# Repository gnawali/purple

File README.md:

# What is this repository for #

This repository contains hardware and software for building practical Visible Light Communication system. The PURPLE board is a cape that works with BeagleBone Black embedded computer. With PURPLE, one can send and receive information using visible light.

The hardware design is available in the eagle folder.

### What's included ###
* Firmware running on PRU including both transmitter and receiver
* User-space program to run on embedded Linux environment 
* Hardware schematic
* Partlist to assemble your own cape [Digi-Key](http://www.digikey.com/short/qq17qj)
* PCB ordering [OSH Park](https://oshpark.com/shared_projects/B5KA0qL4)

### Contents ###

* config/

 This directory contains all configuration files used before make.

* docs/

 This directory contains all documents and notes used as instructions and tutorials deployed in class.

* example/

 This directory contains the userspace program to send and receive msgs through light.

* firmware/

 This directory contains the binary files that's going to run on PRU

* pcb/

 This directory contains the hardware schematic and the PCB layout as well as the partlists.

* src/

 This directory contains the source file that needs to be compiled into the binary file under firmware folder.

* test/

 This directory contains the test and debugging file in user space for the PRU source code.

### How do I get set up? ###

- Summary of set up
    1. Hardware
    	- Beaglebone Black
    	- Purple Cape
    	- SD card
    	- Micro USB cable
    2. Software
	    - BBB Driver[[Windows]](https://learn.adafruit.com/ssh-to-beaglebone-black-over-usb/installing-drivers-windows)[[Mac]](https://learn.adafruit.com/ssh-to-beaglebone-black-over-usb/installing-drivers-mac)[[Linux]](https://learn.adafruit.com/ssh-to-beaglebone-black-over-usb/installing-drivers-linux)
	    - SSH[[Windows]](https://learn.adafruit.com/ssh-to-beaglebone-black-over-usb/ssh-with-windows-and-putty)[[Mac/Linux]](https://learn.adafruit.com/ssh-to-beaglebone-black-over-usb/ssh-on-mac-and-linux) 
    3. Internet Connection (optional)
	    - Ethernet Cable (Required physical access to the LAN port of your router/access point)
	    - [Wireless Dongle](https://learn.adafruit.com/setting-up-wifi-with-beaglebone-black/overview)
    
* Configuration
* Dependencies
* Deployment instructions
  1. LED installation.
  2. Photodiode installation.

### How to get started ###

Step 1: Insert SD card to BBB board. Make sure SD card has been flashed with the purple image.

Step 2: Boot Up the BBB board and connect the board to your PC/Laptop. Make sure you have successfully installed the drivers for BBB.

Step 3: SSH to the board. ssh debian@192.168.7.2

```
ssh debian@192.168.7.2
```
Step 4: When you login, Change to root.

```
sudo -s
```

Step 5: Go to purple repository.

```
cd purple
```

Step 6: Reload the pru remoteproc kernel module.

```
rmmod pru_rproc

modprobe pru_rproc

```

Step 7: Compile the code.
```
make clean
make
```
Step 8: Make sure the code got compiled succesfully.

Step 9: Start listening on incoming messages on one purple board.
```
cd example
./receive
```

Step 10: Start sending the messages on other purple board.
```
cd example
./send "hello world"
```

Step 11: Make sure the message got received correctly.

Step 12: Congratulations. You've completed this short tutorial.

### Who do I talk to? ###

* Shengrong Yin (syin@uh.edu) 
* Omprakash Gnawali (gnawali@cs.uh.edu) 

### References ###

[Exploring Beaglebone](http://exploringbeaglebone.com/chapter13/)

[PRU-ICSS](http://processors.wiki.ti.com/index.php/PRU-ICSS)

[PRU-software-support-package](https://git.ti.com/pru-software-support-package)

[spruhv7a](http://www.ti.com/lit/ug/spruhv7a/spruhv7a.pdf)

[arduino VLC](https://github.com/jpiat/arduino)

[PRU mailing list](https://groups.google.com/forum/#!forum/beagleboard)

[BeagleScope](https://github.com/ZeekHuge/BeagleScope)

[PRUDAQ](https://github.com/google/prudaq/wiki)

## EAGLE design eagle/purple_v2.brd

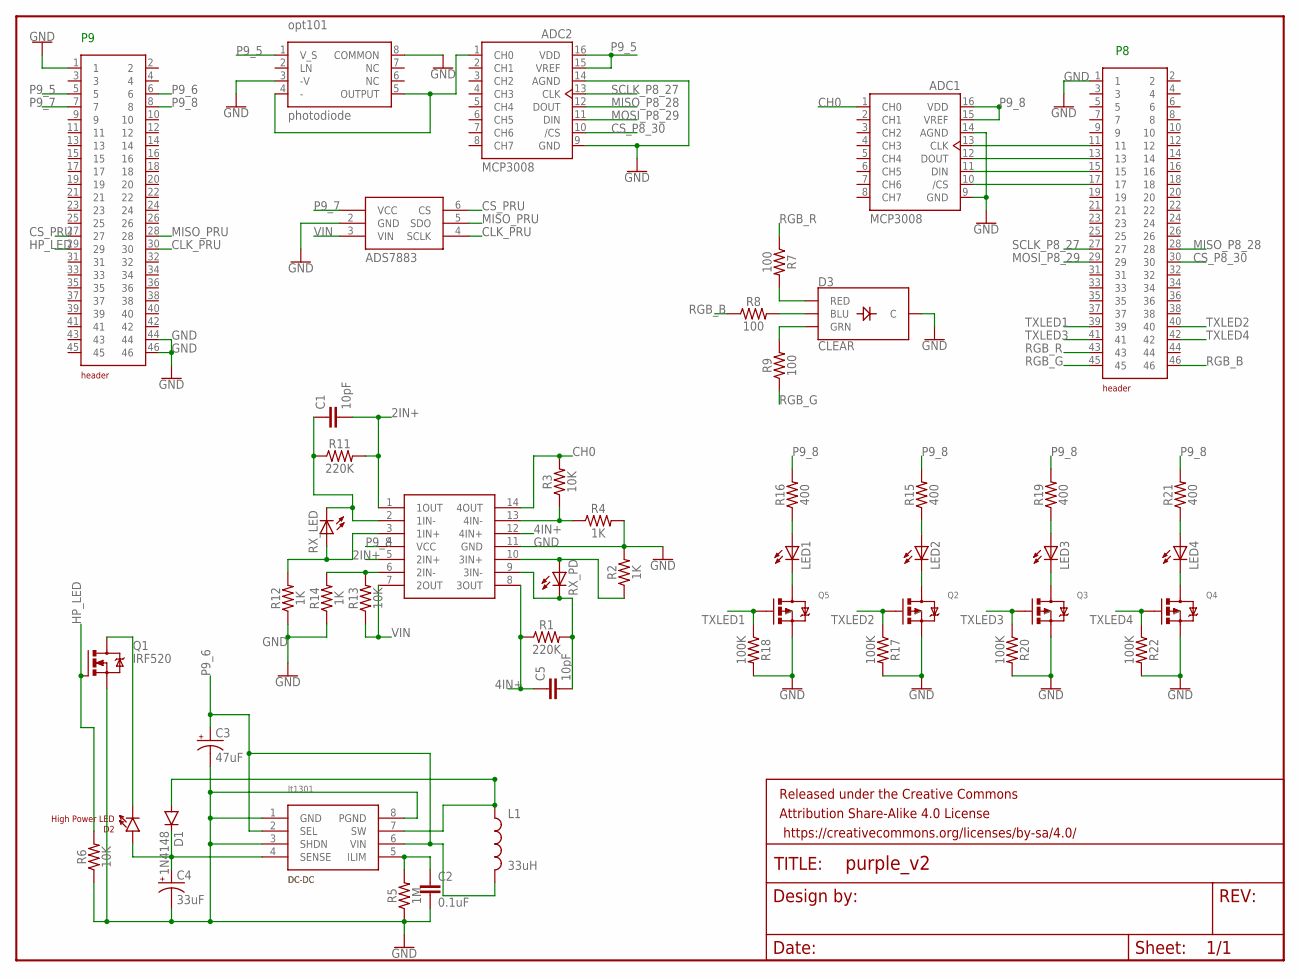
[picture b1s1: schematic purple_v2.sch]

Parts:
ADC1, ADC2: MCP3008-SO16; SO16
C1, C5: 10pF; 0603
C2: 0.1uF; CAP-PTH-SMALL
C3: 47uF; CPOL-RADIAL-10UF-25V
C4: 33uF; CPOL-RADIAL-10UF-25V
D1: 1N4148; DIODE-1N4148
D2: High Power LED; LTE-302
D3: CLEAR; LED-RGB-THRU
FRAME1: FRAME-LETTERNO_PACKAGE; DUMMY
J1, J2: 223; 2*23
L1: 33uH; RLB0912
LED1, LED2, LED3, LED4: LED5MM
OP-AMP: TLC2274-SO14; SO14
Q1: IRF520; TO220BV
Q2, Q3, Q4, Q5: MOSFET-PCHANNEL; SOT23-3
R1, R11: 220K; 0805
R2, R4, R12, R14: 1K; 0805
R3, R6, R13: 10K; 0805
R5: 1M; 0805
R7, R8, R9: 100; 0805
R15, R16, R19, R21: 400; 0805
R17, R18, R20, R22: 100K; 0805
RX_LED: LED5MM
RX_PD: LED5MM
U5: LT1301; DIL08
U9: OPT101
U$1: ADS7883; SOT23-6

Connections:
2IN+: C1.2, OP-AMP.1 (1OUT), OP-AMP.5 (2IN+), R11.2
4IN+: C5.1, OP-AMP.8 (3OUT), OP-AMP.12 (4IN+), R1.1
CH0: ADC1.1 (CH0), OP-AMP.14 (4OUT), R3.2
CLK_1: ADC1.13 (CLK), J2.11
CLK_PRU: J1.30, U$1.4 (SCLK)
CS_1: ADC1.10 (/CS), J2.17
CS_P8_30: ADC2.10 (/CS), J2.30
CS_PRU: J1.27, U$1.6 (CS)
DIN_1: ADC1.11 (DIN), J2.15
DOUT_1: ADC1.12 (DOUT), J2.13
GND: ADC1.9 (GND), ADC1.14 (AGND), ADC2.9 (GND), ADC2.14 (AGND), C2.2, C3.2 (-), C4.2 (-), D3.2 (C), J1.1, J1.44, J1.46, J2.1, OP-AMP.11 (GND), Q1.S, Q2.2 (S), Q3.2 (S), Q4.2 (S), Q5.2 (S), R2.2, R4.2, R5.1, R6.1, R12.1, R14.1, R17.2, R18.2, R20.2, R22.2, U5.1 (GND), U5.3 (SHDN), U5.8 (PGND), U9.3 (-V), U9.8 (COMMON), U$1.2 (GND)
HP_LED: J1.29, Q1.G, R6.2
MISO_P8_28: ADC2.12 (DOUT), J2.28
MISO_PRU: J1.28, U$1.5 (SDO)
MOSI_P8_29: ADC2.11 (DIN), J2.29
unnamed: D3.1 (RED), R7.2
unnamed: OP-AMP.13 (4IN-), R3.1, R4.1
unnamed: D3.4 (BLU), R8.2
unnamed: D3.3 (GRN), R9.2
unnamed: OP-AMP.10 (3IN+), R2.1, RX_PD.A
unnamed: C5.2, OP-AMP.9 (3IN-), R1.2, RX_PD.K (C)
unnamed: C1.1, OP-AMP.2 (1IN-), R11.1, RX_LED.K (C)
unnamed: LED2.A, R15.1
unnamed: OP-AMP.3 (1IN+), R12.2, RX_LED.A
unnamed: OP-AMP.6 (2IN-), R13.2, R14.2
unnamed: LED1.A, R16.1
unnamed: D2.C, Q1.D
unnamed: ADC2.1 (CH0), U9.4 (-), U9.5 (OUTPUT)
unnamed: LED2.K (C), Q2.3 (D)
unnamed: LED1.K (C), Q5.3 (D)
unnamed: LED3.A, R19.1
unnamed: D1.A, L1.1, U5.7 (SW)
unnamed: C4.1 (+), D1.C, D2.A, U5.4 (SENSE)
unnamed: C2.1, R5.2, U5.5 (ILIM)
unnamed: LED3.K (C), Q3.3 (D)
unnamed: LED4.A, R21.1
unnamed: LED4.K (C), Q4.3 (D)
P9_5: ADC2.15 (VREF), ADC2.16 (VDD), J1.5, U9.1 (V_S)
P9_6: C3.1 (+), J1.6, L1.2, U5.2 (SEL), U5.6 (VIN)
P9_7: J1.7, U$1.1 (VCC)
P9_8: ADC1.15 (VREF), ADC1.16 (VDD), J1.8, OP-AMP.4 (VCC), R15.2, R16.2, R19.2, R21.2
RGB_B: J2.46, R8.1
RGB_G: J2.45, R9.1
RGB_R: J2.43, R7.1
SCLK_P8_27: ADC2.13 (CLK), J2.27
TXLED1: J2.39, Q5.1 (G), R18.1
TXLED2: J2.40, Q2.1 (G), R17.1
TXLED3: J2.41, Q3.1 (G), R20.1
TXLED4: J2.42, Q4.1 (G), R22.1
VIN: OP-AMP.7 (2OUT), R13.1, U$1.3 (VIN)

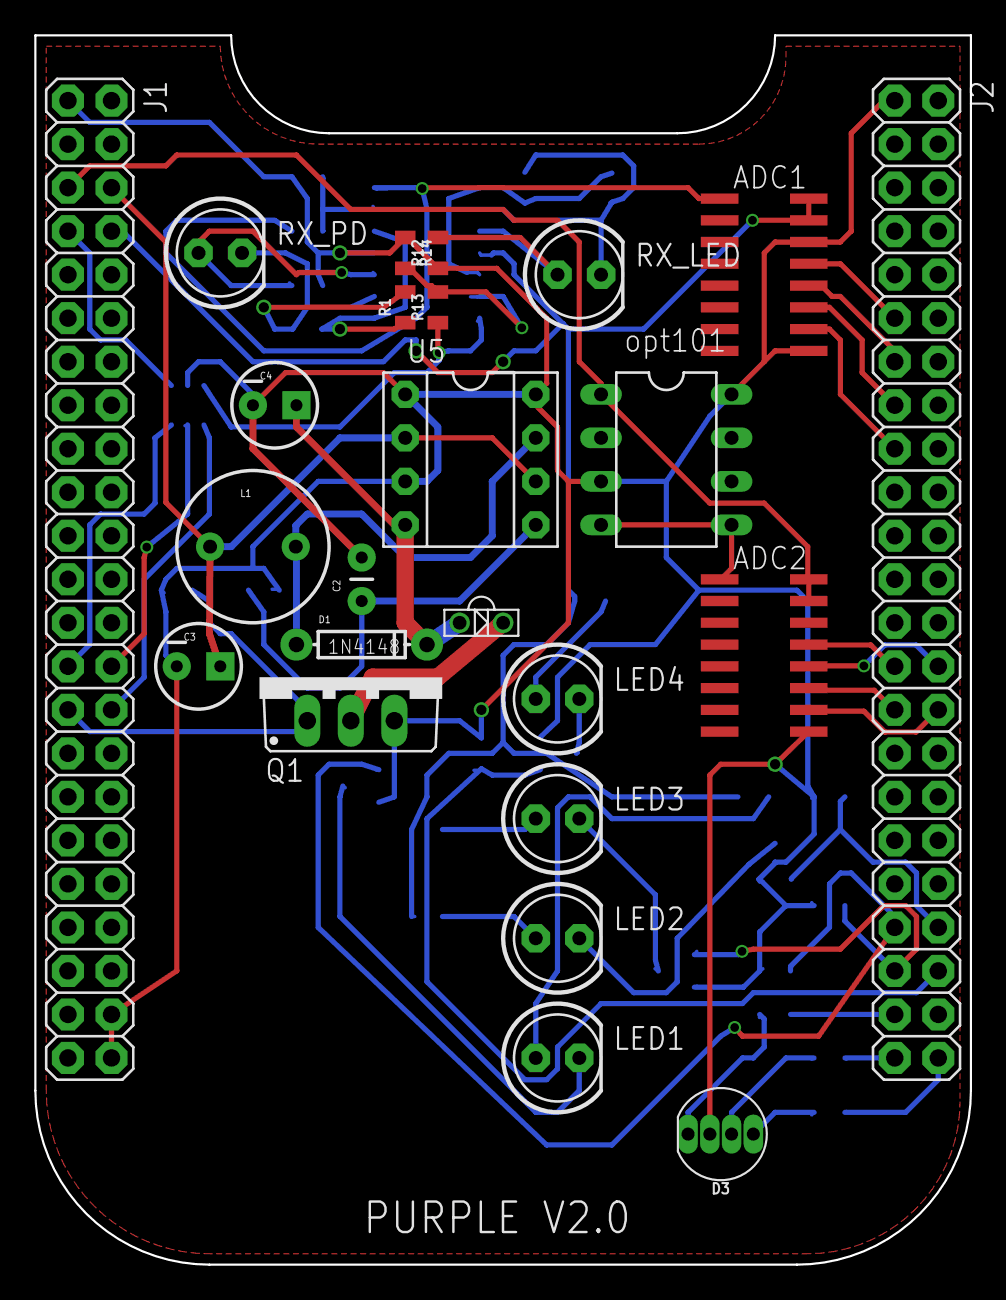
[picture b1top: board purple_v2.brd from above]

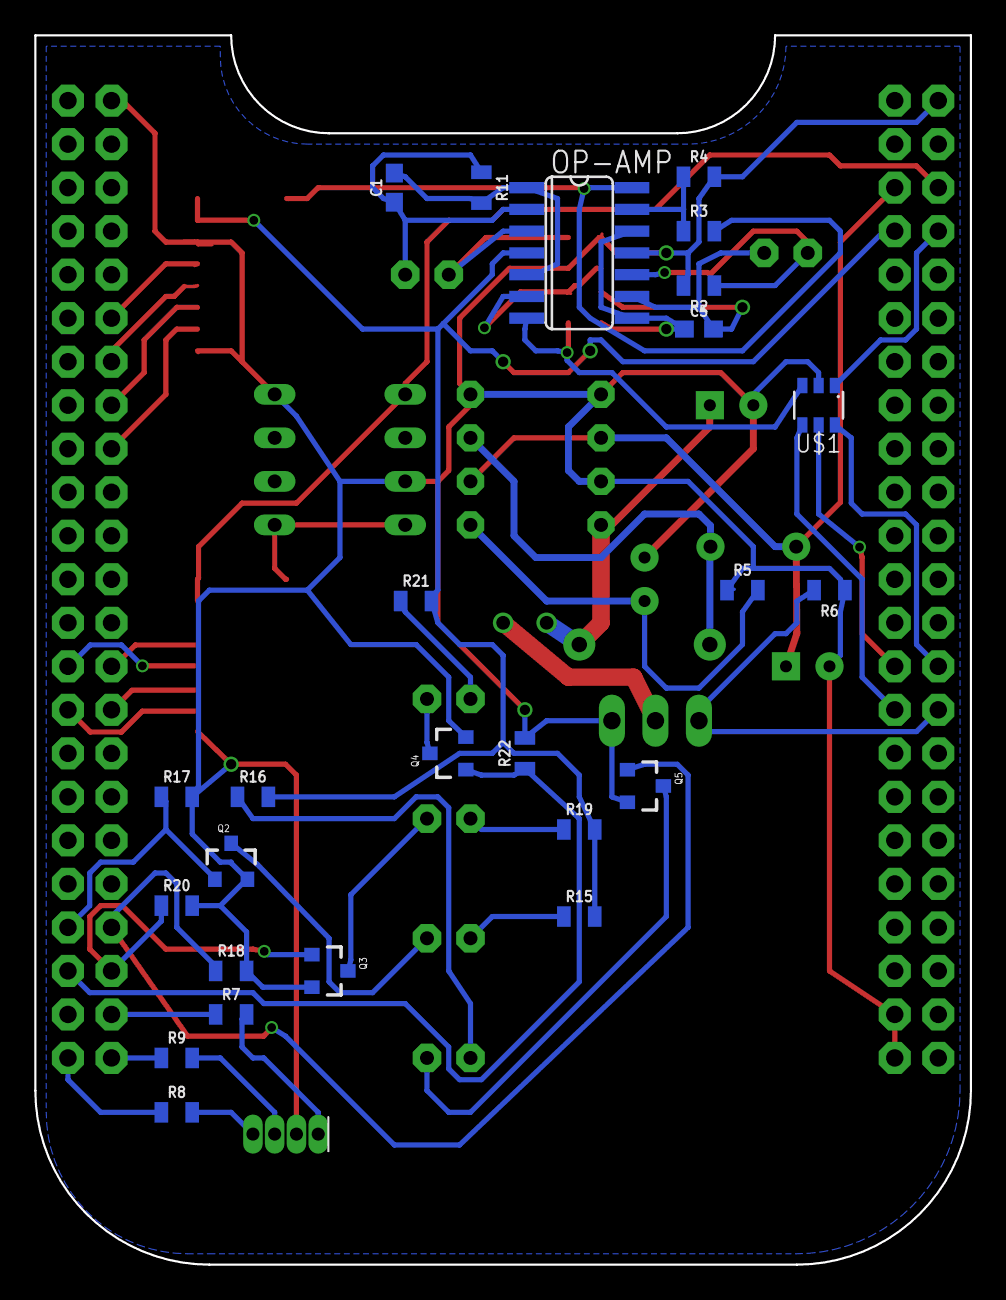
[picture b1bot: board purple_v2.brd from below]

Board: 2 copper layers, 54.6 x 71.8 mm, 50 parts (25 on the bottom side), 50 nets.

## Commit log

2017-03-12 added schematic and board layout...
2017-03-12 move schematic to eagle foler
2017-03-12 removed some file on main folder...
2017-03-28 added bill of materials
2017-03-28 added top and bottom picture for purple v2.0
2017-03-28 added homework from openvlc, actions needed to modify the homework
2017-03-28 Rename Home.md to README.md
2017-04-06 added instruction for PRU based project
2017-04-06 modified hw5
2017-04-07 added image for tutorials
2017-04-07 moved images folder
2017-04-07 added images for tutorials
2017-04-07 moved image folder
2017-04-07 edited filename
2017-04-07 added pictures for tutorials
2017-04-07 added pics for tutorials
2017-04-07 renamed a file
2017-04-07 added a image
2017-04-12 removed sth...
2017-04-13 initial content
2017-04-16 updated image...
2017-04-16 updated readme...
2017-06-21 Add files via upload
    Instructions and walk-through videos for installing and running the sample network project on Beagle Bone Black for both Windows and Mac. Written by Sebastían Rivera González, Emilio Chavez Madero an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
2017-10-04 added lab instruction
2017-10-19 updated doc
2017-10-19 removed duplicates
2017-10-30 add a new project
2017-10-30 Rename project to project.md
2017-10-30 updated project
2017-10-30 added dataflow image
2017-12-31 add src
2017-12-31 edit readme
2017-12-31 add board image
2018-01-01 add order info

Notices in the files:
parts and their libraries:
SparkFun-Resistors: Licensing: Creative Commons ShareAlike 4.0 International - https://creativecommons.org/licenses/by-sa/4.0
SparkFun-Aesthetics: Released under the Creative Commons Attribution Share-Alike 4.0 License
SparkFun-Aesthetics: https://creativecommons.org/licenses/by-sa/4.0
